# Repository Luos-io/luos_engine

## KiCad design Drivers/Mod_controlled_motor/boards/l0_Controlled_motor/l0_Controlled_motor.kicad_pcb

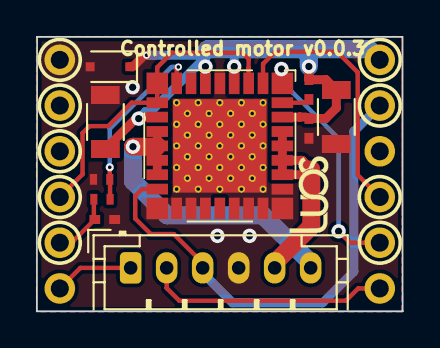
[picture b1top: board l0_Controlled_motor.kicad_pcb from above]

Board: 2 copper layers, 20.3 x 15.2 mm, 11 parts (0 on the bottom side), 13 nets.

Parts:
C1: 0.47uf; C_0402_NoSilk
C2: 33nf; C_0402_NoSilk
C3: 100nf; C_0402_NoSilk
C4, C5: 47uf; C_1206
D1: D_Zener; D_SOD-323F
J1: l0_Socket; l0_Shield_Socket
J2: Header6Contacts; JST_PH_B6B-PH-K_1x06_P2.00mm_Vertical
R1: 1K; R_0402_NoSilk
R2: 220; R_0402_NoSilk
U1: MC33926; 32-PIN_PQFN

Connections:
+3V3: J1.5, J2.3, U1.16
+BATT: C2.1, C3.1, C4.1, C5.1, D1.1, J1.6, U1.4, U1.6, U1.11, U1.31
/A: J1.12, J2.1
/B: J1.1, J2.2
/EN\SLEW: J1.10, U1.3, U1.9, U1.10
/FB: C1.1, J1.11, R1.2
/PWM1: J1.2, U1.1
/PWM2: J1.3, U1.2
GND: C1.2, C3.2, C4.2, C5.2, D1.2, J1.7, J2.4, R2.1, U1.5, U1.17, U1.18, U1.19, U1.20, U1.22, U1.23, U1.24, U1.25, U1.26, U1.33
unnamed: C2.2, U1.32
unnamed: J2.5, U1.27, U1.28, U1.29, U1.30
unnamed: J2.6, U1.12, U1.13, U1.14, U1.15
unnamed: R1.1, R2.2, U1.8

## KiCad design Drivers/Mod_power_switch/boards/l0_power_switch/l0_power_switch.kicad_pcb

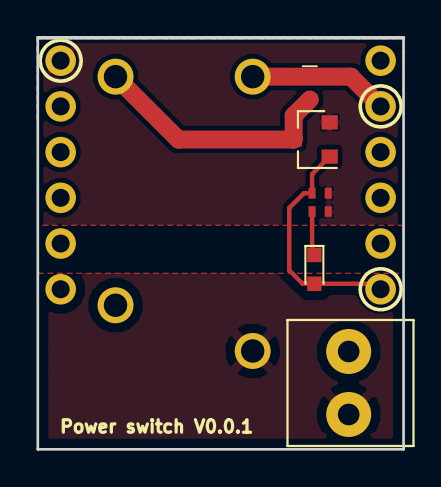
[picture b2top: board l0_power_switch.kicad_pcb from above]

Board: 2 copper layers, 20.3 x 22.9 mm, 8 parts (0 on the bottom side), 7 nets.

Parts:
D1: LED; LED_0603
D2: D_Schottky; D_0603
J1: l0_Socket; l0_Shield_Socket
J2: Screw_Terminal_01x02-Connector_Specialized; 1776275-2
Q1: PMV25ENEA; SOT-23
R1: 82R; R_0402_NoSilk
R2: 10K; R_0402_NoSilk
U1: RelayNO; OJE-SS-103HM,000

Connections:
+3V3: D2.1, J1.5, U1.4
/+: J2.1, U1.3
/-: J2.2, U1.2
GND: J1.7, Q1.2, R1.2, R2.2
unnamed: D1.1, J1.1, Q1.1, R2.1
unnamed: D1.2, R1.1
unnamed: D2.2, Q1.3, U1.1

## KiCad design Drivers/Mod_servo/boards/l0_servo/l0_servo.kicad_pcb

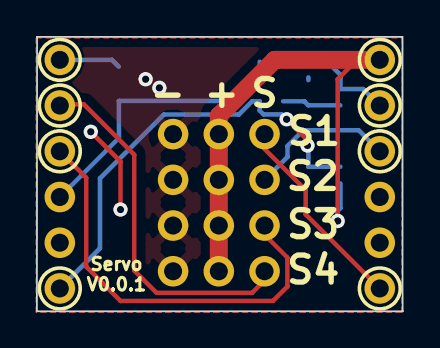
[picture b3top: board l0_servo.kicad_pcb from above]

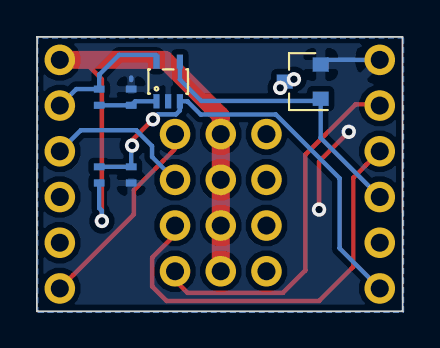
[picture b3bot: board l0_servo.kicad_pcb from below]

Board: 2 copper layers, 20.3 x 15.2 mm, 11 parts (6 on the bottom side), 11 nets.

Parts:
J1: l0_Socket; l0_Shield_Socket
Q1: NMOS_GSD; SOT-23
R1: 20k; R_0402_NoSilk
R2, R4: 10k; R_0402_NoSilk
R3: 68k; R_0402_NoSilk
S1, S2, S3, S4: Header3Contacts; 826926-3
U1: LMV301; SC-70-5

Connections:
+3V3: J1.5, R1.1, U1.5
/V_max: J1.10, Q1.1, U1.4
/V_robus_img: J1.12, R3.2, R4.1, U1.3
GND: J1.7, Q1.2, R2.2, R4.2, U1.2
GNDREF: Q1.3, S1.3, S2.3, S3.3, S4.3
unnamed: J1.1, S1.1
unnamed: J1.4, S2.1
unnamed: J1.8, S4.1
unnamed: J1.9, S3.1
unnamed: R1.2, R2.1, U1.1
VCC: J1.6, R3.1, S1.2, S2.2, S3.2, S4.2

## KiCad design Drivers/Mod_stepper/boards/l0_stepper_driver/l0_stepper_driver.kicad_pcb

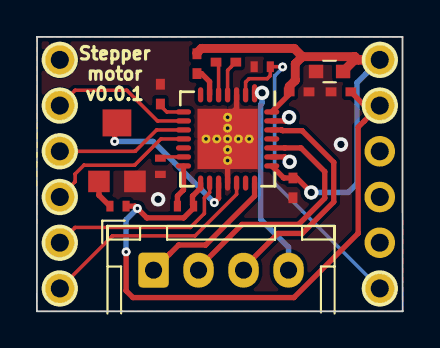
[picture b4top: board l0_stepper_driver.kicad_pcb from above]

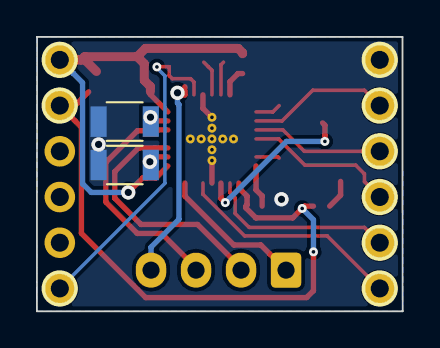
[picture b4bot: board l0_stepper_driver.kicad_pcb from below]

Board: 2 copper layers, 20.3 x 15.2 mm, 18 parts (2 on the bottom side), 23 nets.

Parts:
C1: 10uF; C_0603
C2, C7: 0.1uF; C_0402_NoSilk
C3, C5: 0.1µF; C_0402_NoSilk
C4, C6: 0.22µF; C_0402_NoSilk
J1: l0_Socket; l0_Shield_Socket
J4: Header4Contacts; JST_XH_B04B-XH-A_1x04_P2.50mm_Vertical
R1, R2, R4: 10k; R_0402_NoSilk
R3: 20k; R_0402_NoSilk
R5, R6: 0.5R; R_1206
RV1: 10K; TC33X
U1: A4988; QFN-28-1EP_5x5mm_Pitch0.5mm
U2: radiateur; HEATSINK-A4988

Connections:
+3V3: C6.1, J1.5, R1.2, R3.1, U1.15
/1A: J4.2, U1.24
/1B: J4.1, U1.21
/2A: J4.3, U1.26
/2B: J4.4, U1.1
/DIR: J1.12, U1.19
/MS1: J1.8, U1.9
/MS2: J1.9, U1.10
/MS3: J1.10, U1.11
/Robus_PS: C1.1, C2.1, C5.1, C7.1, J1.6, U1.22, U1.28
/STEP: J1.11, U1.16
/\ENABLE: J1.1, R2.2, U1.2
GND: C1.2, C2.2, C4.2, C6.2, C7.2, J1.7, R2.1, R4.2, R5.1, R6.1, RV1.3, U1.3, U1.18, U1.29
unnamed: C3.1, U1.4
unnamed: C3.2, U1.5
unnamed: C4.1, U1.8
unnamed: C5.2, U1.6
unnamed: R1.1, U1.14
unnamed: R3.2, RV1.1
unnamed: R4.1, U1.13
unnamed: R5.2, U1.27
unnamed: R6.2, U1.23
unnamed: RV1.2, U1.17

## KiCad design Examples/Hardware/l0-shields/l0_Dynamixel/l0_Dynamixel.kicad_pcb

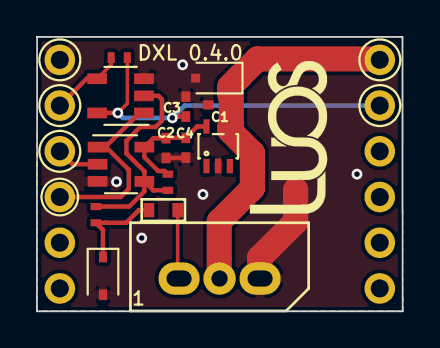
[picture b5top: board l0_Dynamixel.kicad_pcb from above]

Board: 2 copper layers, 20.3 x 15.2 mm, 15 parts (0 on the bottom side), 10 nets.

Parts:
C1, C2, C3: 100nF; C_0402_NoSilk
C4: 0,47µF; C_0402_NoSilk
D1: 5v1; D_SOD-323
D2: D_Zener; D_SOD-323F
J1: l0_Socket; l0_Shield_Socket
J2: DXL; XL320_MX
R1, R5: 10K; R_0402_NoSilk
R2: 150; R_0402_NoSilk
TH1: 100; PRG18_RB
U1: TPS71550DCKR; SC-70-5
U2: SN74LVC1G126DBVT; SOT-23-5
U3: SN74LVC1G125DBVR; SOT-23-5

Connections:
+3V3: C3.1, J1.5, R5.1, U3.5
+5V: C2.1, C4.1, R1.1, U1.5, U2.5
/DX_DATA: J2.1, TH1.2
/DX_DIR: J1.10, U2.1, U3.1
/RxD_3v3: J1.8, R5.2, U3.4
/TxD_3v3: J1.9, U2.2
/V_Robus: C1.1, D2.1, J1.6, J2.2, U1.4
GND: C1.2, C2.2, C3.2, C4.2, D1.2, D2.2, J1.7, J2.3, U1.2, U2.3, U3.3
unnamed: D1.1, R2.1, TH1.1
unnamed: R1.2, R2.2, U2.4, U3.2

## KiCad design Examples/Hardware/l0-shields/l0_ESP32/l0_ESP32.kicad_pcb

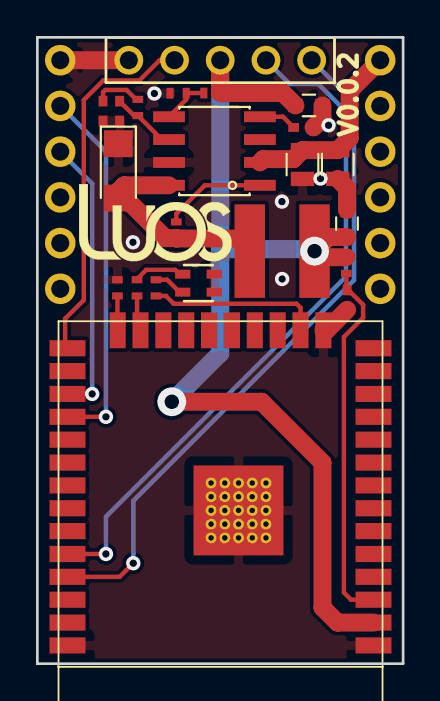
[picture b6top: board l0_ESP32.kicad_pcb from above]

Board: 2 copper layers, 20.3 x 34.8 mm, 23 parts (0 on the bottom side), 20 nets.

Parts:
C1: 100nf; C_0402_NoSilk
Cboot1: 100nF; R_0402_NoSilk
Ccomp1: 1.8nF; C_0402_NoSilk
Ccomp2: 33pf; C_0402_NoSilk
Cin1, Cin2: 10uf; R_0805
Cout1, Cout2: 22uF; C_0603
Css1: 8.2nF; C_0402_NoSilk
D1: KPTB-1615ESGC
D2: D_Schottky; SOD-123F
J1: l0_Socket; l0_Shield_Socket
J2: Header5Contacts; 826926-5
L1: 12uH; SRR4528A
R1, R3: 10K; R_0402_NoSilk
R2: 66,5; R_0402_NoSilk
R5: 56; R_0402_NoSilk
Rcomp1: 18.7k; R_0402_NoSilk
Rfbb1: 3.24k; R_0402_NoSilk
Rfbt1: 10.2K; R_0402_NoSilk
U1: esp32; ESP32-WROOM-32D
U2: TPS54232; SO8

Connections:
+3V3: Cout1.1, Cout2.1, J2.3, L1.2, R1.1, Rfbt1.1, U1.2
/RX: J2.5, U1.35
/RX_L0: J1.8, U1.28
/TX: J2.4, U1.34
/TX_L0: J1.9, U1.27
/prog_mode: J2.2, U1.25
GND: C1.2, Ccomp1.2, Ccomp2.1, Cin1.2, Cin2.2, Cout1.2, Cout2.2, Css1.2, D1.2, D1.4, D2.2, J1.7, J2.1, R3.1, Rfbb1.2, U1.1, U1.15, U1.38, U1.39, U2.7
unnamed: C1.1, R1.2, U1.3
unnamed: Cboot1.1, U2.1
unnamed: Cboot1.2, D2.1, L1.1, U2.8
unnamed: Ccomp1.1, Rcomp1.2
unnamed: Ccomp2.2, Rcomp1.1, U2.6
unnamed: Css1.1, U2.4
unnamed: D1.1, R2.2
unnamed: D1.3, R5.2
unnamed: R2.1, U1.16
unnamed: R3.2, U1.24
unnamed: R5.1, U1.23
unnamed: Rfbb1.1, Rfbt1.2, U2.5
VCC: Cin1.1, Cin2.1, J1.6, U2.2

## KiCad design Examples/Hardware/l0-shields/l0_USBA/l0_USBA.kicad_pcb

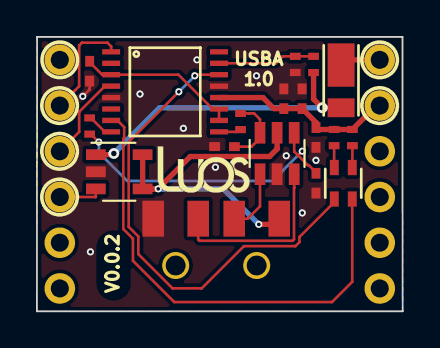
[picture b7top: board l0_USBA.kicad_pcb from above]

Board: 2 copper layers, 20.3 x 15.2 mm, 19 parts (0 on the bottom side), 20 nets.

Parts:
C1, C2: 47pF; C_0402_NoSilk
C3, C4, C5: 100nF; C_0402_NoSilk
C6: 4.7uF; C_0402_NoSilk
D1: KPTB-1615ESGC
D2: DFLS230L-7; PowerDI-123
J1: USB_A; USBA_SMD
J2: l0_Shield_Socket
R1, R2: 27; R_0402_NoSilk
R3: 4K7; R_0402_NoSilk
R4: 10K; R_0402_NoSilk
R5: 66,5; R_0402_NoSilk
R6: 56; R_0402_NoSilk
U1: FT230X; SSOP-16
U2: STMPS2171STR; SOT-23-5
U3: USBLC6-2SC6; SOT23-6L

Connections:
+3V3: C4.1, C5.1, C6.1, J2.5, R5.1, R6.1, U1.12
+5V: J1.1, U2.4, U2.5, U3.5
/RxD: J2.9, U1.4
/Rx_LED: D1.4, U1.7
/TxD: J2.8, U1.1
/Tx_LED: D1.2, U1.14
/Vin: D2.1, J2.6
GND: C1.2, C2.2, C3.2, C4.2, C5.2, C6.2, J1.4, J2.7, R4.1, U1.5, U1.13, U2.2, U3.2
unnamed: C1.1, R2.2, U3.6
unnamed: C2.1, R1.2, U3.4
unnamed: C3.1, U1.3, U1.10, U1.11
unnamed: D1.1, R5.2
unnamed: D1.3, R6.2
unnamed: J1.2, U3.1
unnamed: J1.3, U3.3
unnamed: J2.10, U2.3
unnamed: R1.1, U1.8
unnamed: R2.1, U1.9
unnamed: R3.1, R4.2, U1.15
VBUS: D2.2, R3.2, U2.1
